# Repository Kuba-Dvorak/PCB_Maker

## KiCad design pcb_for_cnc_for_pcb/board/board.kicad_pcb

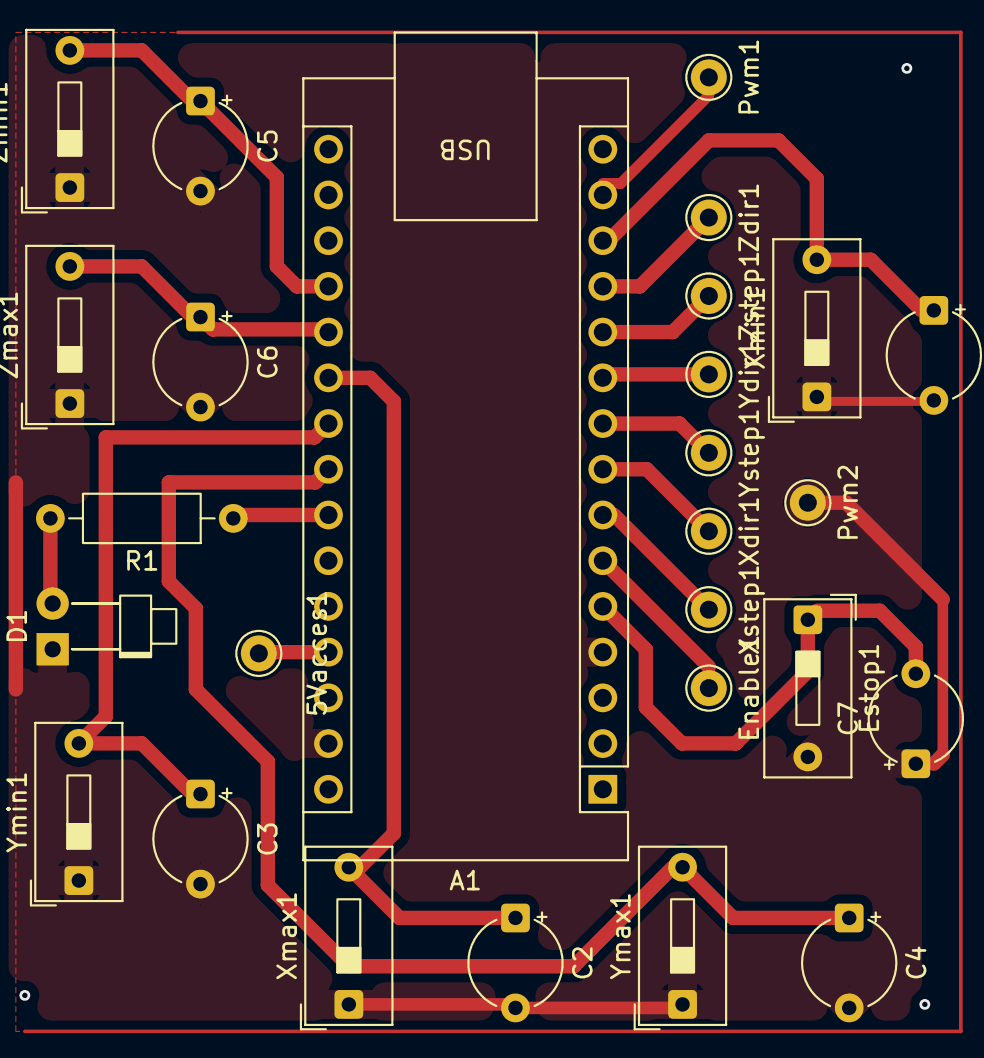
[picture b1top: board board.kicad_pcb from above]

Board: 2 copper layers, 27 parts (0 on the bottom side), 19 nets.

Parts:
5Vacces1: TestPoint; Pin_D1.0mm_L10.0mm
A1: arduino; Arduino_Nano
C1, C2, C3, C4, C5, C6, C7: C_Small; CP_Radial_Tantal_D5.0mm_P5.00mm
D1: LED; LED_D1.8mm_W1.8mm_H2.4mm_Horizontal_O3.81mm_Z1.6mm
Enable1: TestPoint; Pin_D1.0mm_L10.0mm
Estop1: SW_Push; SW_DIP_SPSTx01_Slide_9.78x4.72mm_W7.62mm_P2.54mm
Pwm1, Pwm2: TestPoint; Pin_D1.0mm_L10.0mm
R1: R; R_Axial_DIN0207_L6.3mm_D2.5mm_P10.16mm_Horizontal
Xdir1: TestPoint; Pin_D1.0mm_L10.0mm
Xmax1: SW_Push; SW_DIP_SPSTx01_Slide_9.78x4.72mm_W7.62mm_P2.54mm
Xmin1: SW_Push; SW_DIP_SPSTx01_Slide_9.78x4.72mm_W7.62mm_P2.54mm
Xstep1: TestPoint; Pin_D1.0mm_L10.0mm
Ydir1: TestPoint; Pin_D1.0mm_L10.0mm
Ymax1: SW_Push; SW_DIP_SPSTx01_Slide_9.78x4.72mm_W7.62mm_P2.54mm
Ymin1: SW_Push; SW_DIP_SPSTx01_Slide_9.78x4.72mm_W7.62mm_P2.54mm
Ystep1: TestPoint; Pin_D1.0mm_L10.0mm
Zdir1: TestPoint; Pin_D1.0mm_L10.0mm
Zmax1: SW_Push; SW_DIP_SPSTx01_Slide_9.78x4.72mm_W7.62mm_P2.54mm
Zmin1: SW_Push; SW_DIP_SPSTx01_Slide_9.78x4.72mm_W7.62mm_P2.54mm
Zstep1: TestPoint; Pin_D1.0mm_L10.0mm

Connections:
unnamed: A1.19 (A0), C5.1, Zmin1.2
unnamed: A1.20 (A1), C6.1, Zmax1.2
unnamed: A1.21 (A2), C2.1, Xmax1.2
unnamed: A1.22 (A3), C3.1, Ymin1.2
unnamed: A1.5 (D2), C7.2, Estop1.1
unnamed: A1.6 (D3), Enable1.1 (1_1)
unnamed: A1.7 (D4), Xstep1.1 (1_1)
unnamed: A1.8 (D5), Xdir1.1 (1_1)
unnamed: A1.9 (D6), Ystep1.1 (1_1)
unnamed: A1.10 (D7), Ydir1.1 (1_1)
unnamed: A1.11 (D8), Zstep1.1 (1_1)
unnamed: A1.12 (D9), Zdir1.1 (1_1)
unnamed: A1.13 (D10/CS), C1.1, Xmin1.2
unnamed: A1.14 (D11/COPI), Pwm1.1 (1_1)
unnamed: A1.24 (SCL/A5), R1.1
unnamed: A1.23 (SDA/A4), C4.1, Ymax1.2
unnamed: 5Vacces1.1 (1_1), A1.27 (VUSB/5V)
unnamed: D1.2 (A), R1.2
unnamed: A1.4 (GND), A1.29 (GND), C1.2, C2.2, C3.2, C4.2, C5.2, C6.2, C7.1, D1.1 (K), Estop1.2, Pwm2.1 (1_1), Xmax1.1, Xmin1.1, Ymax1.1, Ymin1.1, Zmax1.1, Zmin1.1
